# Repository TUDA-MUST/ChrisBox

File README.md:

# ChrisBox
(**CH**arge **R**eading **I**nferface **S**ystem Box)\
4-Channel Charge Amplifier PCB

## Introduction

Welcome to ChrisBox!\
ChrisBox is a four-channel charge amplifier, mainly developed for the simultaneous charge measurement of four ferroelectret sensors.
The main goals of the development were
- low noise (shielding concept),
- portability,
- usability,
- affordability.

More details about ChrisBox can be found [here](#about-chrisbox).

> [!IMPORTANT]
> This document describes the features and assembly of ChrisBox and does not provide guidance on constructing or using ferroelectret sensors.

## About this Repository

This repository contains the PCB design of ChrisBox, the CAD files for the Box, where the PCB can be combined with a battery and a display, as well as general code for the PCB.
- [PCB](/PCB) -> circuit board
- [CAD](/CAD) -> housing for the circuit board and an additional display
- [CODE](/CODE) -> code to be flashed on the microcontroller of the PCB, and code for a Nextion display.

A code description is found in the `./CODE` folder, if you just want to build a ChrisBox, the following instructions should be sufficient.

Ordering and Building instructions are included here:
- [ORDERING INSTRUCTIONS](/ORDERING_INSTRUCTIONS.md)
- [BUILDING INSTRUCTIONS](/BUILDING_INSTRUCTIONS.md)

Contributing to ChrisBox and this repository: [CONTRIBUTORS](#contributors).\
License: [LICENSE](/LICENSE).

Information about citation is found here: [CITATION](#citation).

## About ChrisBox

### Development objective and target group

Piezoelectric sensors convert electric charge in response to mechanical loading and are widely studied for their high sensitivity.
In particular, ferroelectret sensors provide the flexibility and material system design that enable biocompatibility.
These signals are typically captured using commercial electrometers or custom-built charge amplifiers to enable portability.
However, the latter often lack the precision and robustness against electromagnetic interference (EMI).
Therefore, we present a compact, four-channel portable measurement system specifically designed for charge-based force sensing with piezoelectric sensors, called ChrisBox.
The system has been developed at the **Measurement and Sensor Technology Group** at **Technische Universität Darmstadt**, Darmstadt, Germany.

The main goals of the development were:
- **Low noise:** achieved through a shielding concept that covers the PCB, the cable to the sensor, and, depending on the sensor, the sensor itself.
- **Portability:** a key advantage over traditional electrometers and oscilloscopes, enabling measurements on the human body while walking or performing other movements.
- **Usability:** the PCB is designed for users without expertise in PCB development or programming, allowing straightforward measurements with ferroelectret sensors.
- **Affordability:** one assembled PCB costs roughly 50 euros in 2025, facilitating reproduction and simultaneous use while avoiding the need for expensive laboratory instruments such as electrometers.

### Detailed decription of ChrisBox

**Analog electronics**
A ferroelectret is connected to the PCB via a USB-C cable and connector.
The signal wires, D+ and D-, carry the charge displacement generated by the ferroelectret, which is converted into a voltage signal by a charge amplifier.
An exemplary application of this setup is heart rate measurement, which requires low-frequency measurements.
Therefore, a large feedback resistor (in the G&Omega; range) is used in the charge amplifier.
A reference voltage at the midpoint of the measurement range (around 1.65 V) is provided to enable differential measurements within the 0–3.3 V range.
The analog electronics are replicated four times, with each channel operating independently.

**Digital electronics**
The output of each charge amplifier is connected to an ADC (ADS1220).
The reference voltage is also supplied to the ADC to enable differential measurements.
All four ADCs communicate with an ESP32 via SPI.

**ESP32**
An ESP32 S3 Mini 1 serves as the microcontroller of the ChrisBox, accompanied by Boot and Reset buttons.
A UART-to-USB converter ensures reliable connectivity with various PCs.

**Support circuits**
The PCB includes several additional circuits: four programmable status LEDs controlled by the ESP32, a UART connector for interfacing with a Nextion display, and a connector providing access to five GPIO pins of the ESP32 for custom functions.
A 5 V supply, switchable by the ESP32, can power the Nextion display.
A battery can be connected for power supply and is simultaneously charged when the board is connected to USB.

**Shielding**
The PCB is shielded by a metallic frame and cover, as well as an internal shielding layer within the board.
USB-C cables are used to connect the ferroelectret sensors, as they are both shielded and readily available.
Each ferroelectret sensor must be soldered to a USB-C connector.
Since an unshielded ferroelectret sensor can act as a source of noise, proper shielding is essential to ensure a low-noise measurement setup.

**Data output**
The acquired measurement data can be output in several ways:
- Serial communication to a PC,
- UART connection to a Nextion display for real-time visualization,
- ESP-NOW for wireless data transmission, requiring a second ESP32 as receiver for the data, which itself could communicate to a PC.

## Contributors

ChrisBox was developed at the [Measurement and Sensor Technology Group](https://www.etit.tu-darmstadt.de/must/) at Technische Universität Darmstadt, Germany, by:
- [Sven Suppelt](https://orcid.org/0000-0002-2338-9333)
- [Dominik Werner](https://orcid.org/0009-0001-8082-5584)
- [Alexander A. Altmann](https://orcid.org/0000-0001-5299-3620)
- [Felix Herbst](https://orcid.org/0000-0003-1480-3691)
- [Jan H. Dörsam](https://orcid.org/0000-0001-9807-6641)
- [Bastian Latsch](https://orcid.org/0000-0001-9929-5694)
- [Prof. Mario Kupnik](https://orcid.org/0000-0003-2287-4481)

## Citation

If you would like to reference the project, please cite DOI: [10.3390/hardware4040020](https://doi.org/10.3390/hardware4040020).

```
@article{hardware4040020,
  author = {Suppelt, Sven and Werner, Dominik and Altmann, Alexander Anton and Herbst, Felix and Ulmer, Lukas and Dörsam, Jan Helge and Latsch, Bastian and Kupnik, Mario},
  title = {ChrisBox: An Open-Source 4-Channel Portable Charge Amplifier for Research and Education},
  journal = {Hardware},
  year = {2026},
  volume = {4},
  number = {4},
  pages = {20},
  doi = {10.3390/hardware4040020}
}
```

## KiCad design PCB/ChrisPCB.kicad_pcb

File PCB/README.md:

# PCB

Welcome to the PCB folder of ChrisBox!
The ChrisBox PCB is designed with KiCad. The Project files and generated Exports are found here.

## Content of the PCB folder

- `./data` - pictures of the PCB and some for the schematic and silkscreen.
- `./exports` - The `.step`-export of the ChrisBox PCB.
- `./interactive bom` - The interactive HTML BOM (made with Interactive Html Bom). It is useful for handsoldering or just looking up which component has to go where.
- `./jlcpcb` - Output data from the KiCAD JLCPCB tools. This data can be used for ordering a PCB with components. Always re-check the data yourself!
- `./models` - Additional footprints and models, which are not included in KiCad and its plugins itself.

The other files in this folder are the [main KiCad project](/PCB/ChrisPCB.kicad_pro) with schematic and pcb, as well as the sub-schematics (ferro_amplifier and usb_connector).

## Notes on KiCad settings

The design was made with KiCad 8.0. Installed plugins are the Alternate KiCad Library (by Dawid Cislo), the Interactive Html Bom (by qu1ck) and the KiCAD JLCPCB tools (by Bouni).
Additional Footprints or 3D models are found in the `./models` folder.\
Always check the JLCPCB options yourself! The tools seemed to "forget" some data from time to time.

## Ordering and building the PCB

For ordering instructions refer to [ORDERING INSTRUCTIONS](/ORDERING_INSTRUCTIONS.md).
For building instructions refer to [BUILDING INSTRUCTIONS](/BUILDING_INSTRUCTIONS.md).

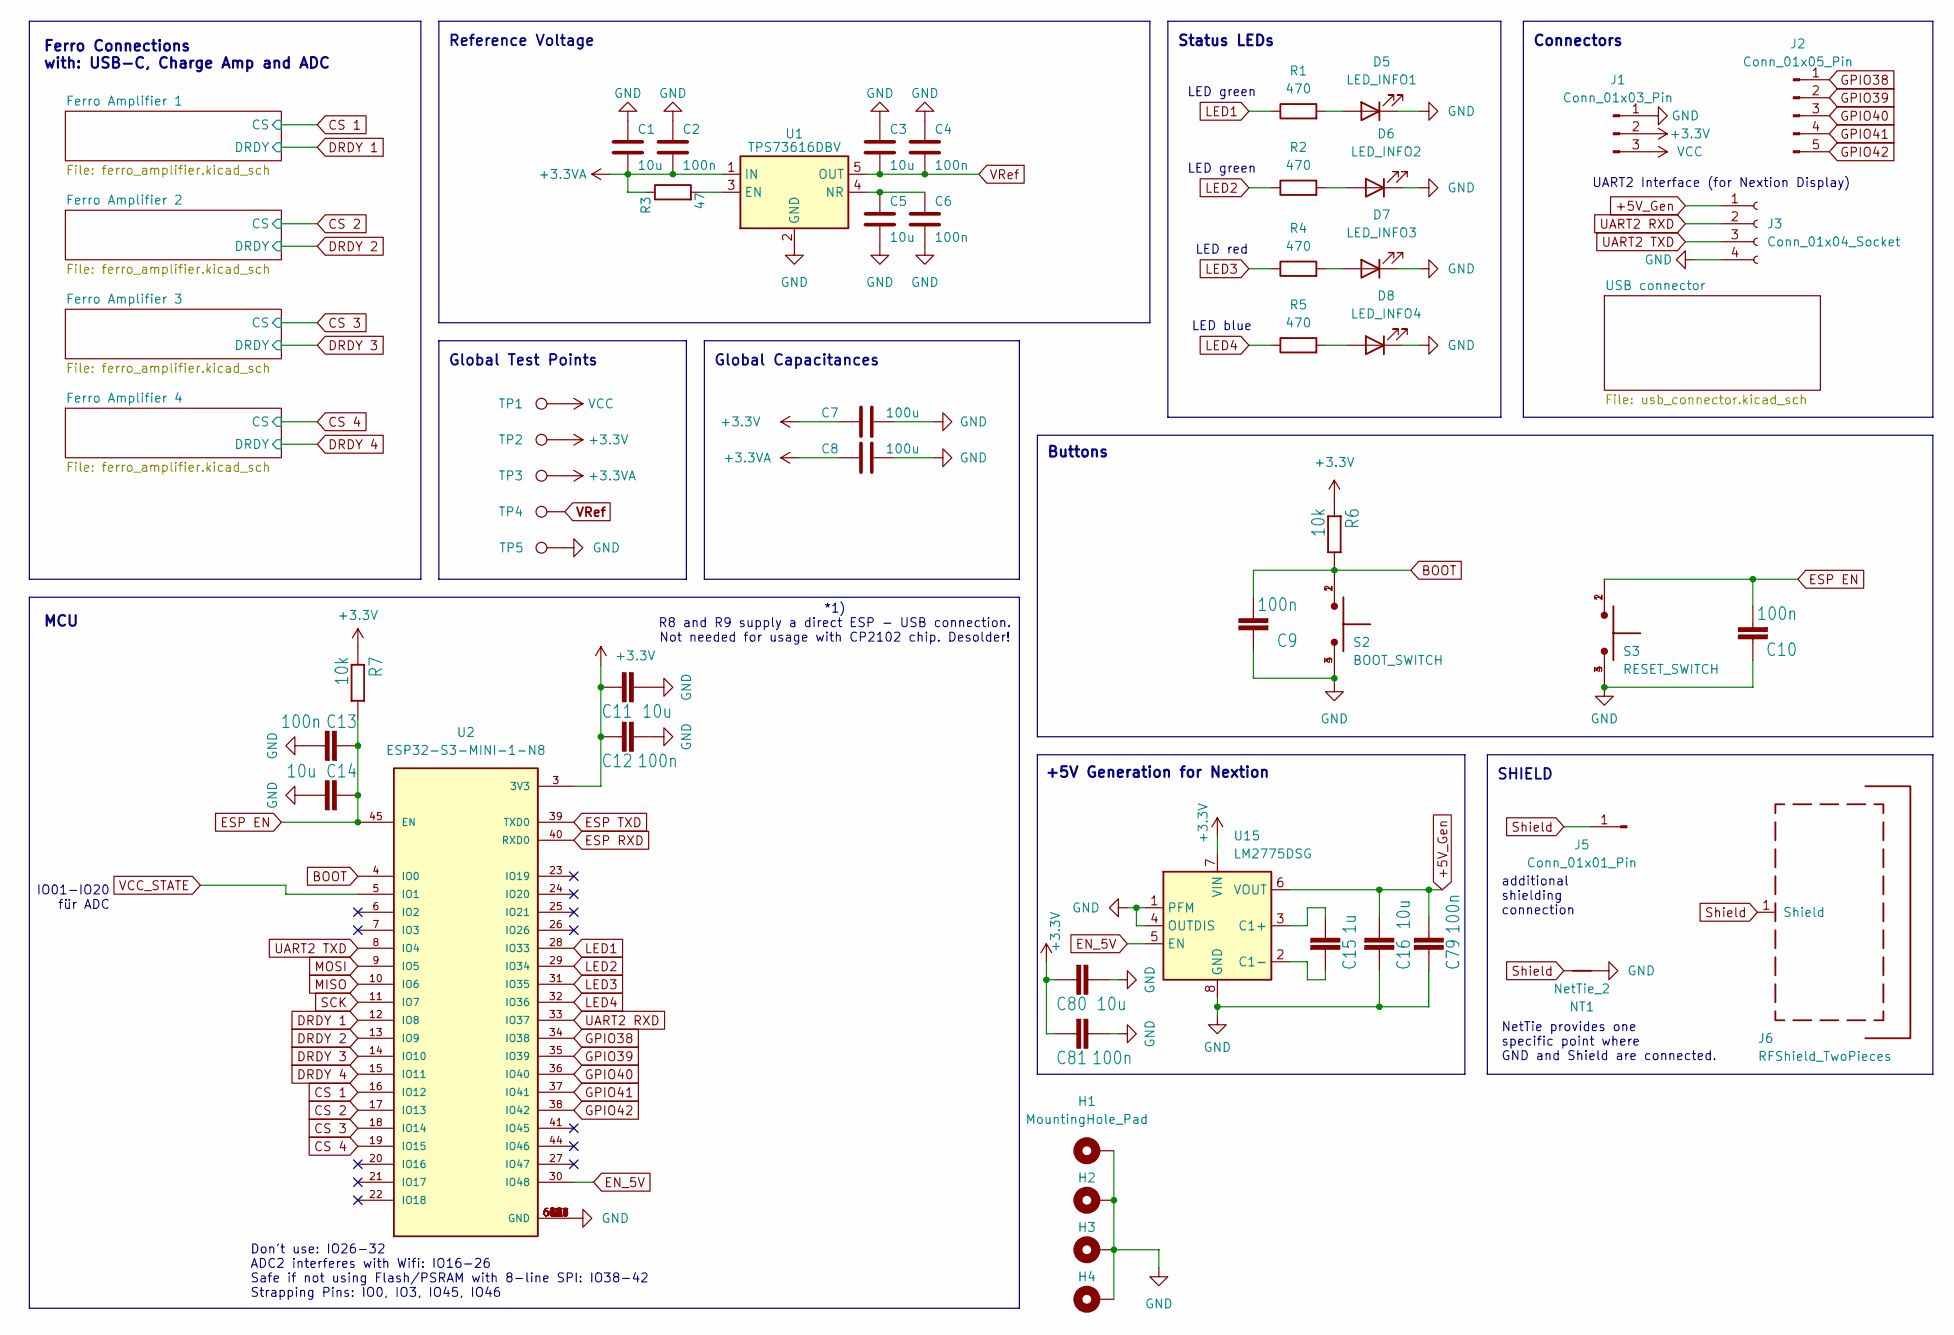
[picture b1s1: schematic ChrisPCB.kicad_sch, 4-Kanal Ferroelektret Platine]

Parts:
C1, C3, C5, C11, C14, C16, C80: 10u; C_0402_1005Metric
C2, C4, C6, C9, C10, C12, C13, C79, C81: 100n; C_0402_1005Metric
C7, C8: 100u; C_1206_3216Metric
C15: 1u; C_0402_1005Metric
D5: LED_INFO1; LED_0402_1005Metric
D6: LED_INFO2; LED_0402_1005Metric
D7: LED_INFO3; LED_0402_1005Metric
D8: LED_INFO4; LED_0402_1005Metric
H1, H2, H3, H4: MountingHole_Pad; MountingHole_3.2mm_M3_Pad
J1: Conn_01x03_Pin; PinHeader_1x03_P2.54mm_Vertical
J2: Conn_01x05_Pin; PinHeader_1x05_P2.54mm_Vertical
J3: Conn_01x04_Socket; JST_XH_B4B-XH-A_1x04_P2.50mm_Vertical
J5: Conn_01x01_Pin; PinHeader_1x01_P2.54mm_Vertical
J6: RFShield_TwoPieces; Laird_Technologies_BMI-S-205-F_38.10x25.40mm_HandSolder_Sel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
NT1: NetTie_2; NetTie-2_SMD_Pad0.5mm
R1, R2, R4, R5: 470; R_0402_1005Metric
R3: 47; R_0402_1005Metric
R6, R7: 10k; R_0402_1005Metric
S2: BOOT_SWITCH; SW_SKRPABE010
S3: RESET_SWITCH; SW_SKRPABE010
TP1, TP2, TP3, TP4, TP5: TestPoint; TestPoint_THTPad_D1.5mm_Drill0.7mm
U1: TPS73616DBV; SOT-23-5
U2: ESP32-S3-MINI-1-N8; XCVR_ESP32-S3-MINI-1-N8; PARTREV v0.6
U15: LM2775DSG; WSON-8-1EP_2x2mm_P0.5mm_EP0.9x1.6mm_ThermalVias

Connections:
+3.3V: C7.1, C11.2, C12.2, C80.2, C81.2, J1.2, R6.1, R7.1, TP2.1, U2.3 (3V3), U15.7 (VIN); also elsewhere on the board
+3.3VA: C1.2, C2.2, C8.1, R3.1, TP3.1, U1.1 (IN); also elsewhere on the board
+5V_Gen: C16.1, C79.1, J3.1, U15.6 (VOUT)
BOOT: C9.2, R6.2, S2.1, S2.2, U2.4 (IO0); also elsewhere on the board
CS 1: U2.16 (IO12); also elsewhere on the board
CS 2: U2.17 (IO13); also elsewhere on the board
CS 3: U2.18 (IO14); also elsewhere on the board
CS 4: U2.19 (IO15); also elsewhere on the board
DRDY 1: U2.12 (IO8); also elsewhere on the board
DRDY 2: U2.13 (IO9); also elsewhere on the board
DRDY 3: U2.14 (IO10); also elsewhere on the board
DRDY 4: U2.15 (IO11); also elsewhere on the board
EN_5V: U2.30 (IO48), U15.5 (EN)
ESP EN: C10.2, C13.2, C14.2, R7.2, S3.1, S3.2, U2.45 (EN); also elsewhere on the board
ESP RXD: U2.40 (RXD0); also elsewhere on the board
ESP TXD: U2.39 (TXD0); also elsewhere on the board
GND: C1.1, C2.1, C3.1, C4.1, C5.2, C6.2, C7.2, C8.2, C9.1, C10.1, C11.1, C12.1, C13.1, C14.1, C16.2, C79.2, C80.1, C81.1, D5.1 (K), D6.1 (K), D7.1 (K), D8.1 (K), H1.1, H2.1, H3.1, H4.1, J1.1, J3.4, NT1.1, S2.3, S2.4, S3.3, S3.4, TP5.1, U1.2 (GND), U2.1 (GND), U2.2 (GND), U2.42 (GND), U2.43 (GND), U2.46 (GND), U2.47 (GND), U2.48 (GND), U2.49 (GND), U2.50 (GND), U2.51 (GND), U2.52 (GND), U2.53 (GND), U2.54 (GND), U2.55 (GND), U2.56 (GND), U2.57 (GND), U2.58 (GND), U2.59 (GND), U2.60 (GND), U2.61 (GND), U2.61_1 (GND), U2.61_2 (GND), U2.61_3 (GND), U2.61_4 (GND), U2.61_5 (GND), U2.61_6 (GND), U2.61_7 (GND), U2.61_8 (GND), U2.62 (GND), U2.63 (GND), U2.64 (GND), U2.65 (GND), U15.1 (PFM), U15.4 (OUTDIS), U15.8 (GND), U15.9 (GND); also elsewhere on the board
GPIO38: J2.1, U2.34 (IO38)
GPIO39: J2.2, U2.35 (IO39)
GPIO40: J2.3, U2.36 (IO40)
GPIO41: J2.4, U2.37 (IO41)
GPIO42: J2.5, U2.38 (IO42)
LED1: R1.1, U2.28 (IO33)
LED2: R2.1, U2.29 (IO34)
LED3: R4.1, U2.31 (IO35)
LED4: R5.1, U2.32 (IO36)
MISO: U2.10 (IO6); also elsewhere on the board
MOSI: U2.9 (IO5); also elsewhere on the board
unnamed: D5.2 (A), R1.2
unnamed: D6.2 (A), R2.2
unnamed: D7.2 (A), R4.2
unnamed: D8.2 (A), R5.2
unnamed: R3.2, U1.3 (EN)
unnamed: C5.1, C6.1, U1.4 (NR)
unnamed: C15.1, U15.3 (C1+)
unnamed: C15.2, U15.2 (C1-)
SCK: U2.11 (IO7); also elsewhere on the board
Shield: J5.1, J6.1 (Shield), NT1.2; also elsewhere on the board
UART2 RXD: J3.2, U2.33 (IO37)
UART2 TXD: J3.3, U2.8 (IO4)
VCC: J1.3, TP1.1; also elsewhere on the board
VCC_STATE: U2.5 (IO1); also elsewhere on the board
VRef: C3.2, C4.2, TP4.1, U1.5 (OUT); also elsewhere on the board

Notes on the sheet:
+5V Generation for Nextion
Global Capacitances
Global Test Points
Buttons
LED green
Reference Voltage
Ferro Connections with: USB-C, Charge Amp and ADC
NetTie provides one specific point where GND and Shield are connected.
Status LEDs
IO01-IO20 für ADC
MCU
SHIELD
Don't use: IO26-32 ADC2 interferes with Wifi: IO16-26 Safe if not using Flash/PSRAM with 8-line SPI: IO38-42 Strapping Pins: IO0, IO3, IO45, IO46
additional shielding connection
LED blue
*1) R8 and R9 supply a direct ESP - USB connection. Not needed for usage with CP2102 chip. Desolder!
Connectors
LED red
UART2 Interface (for Nextion Display)

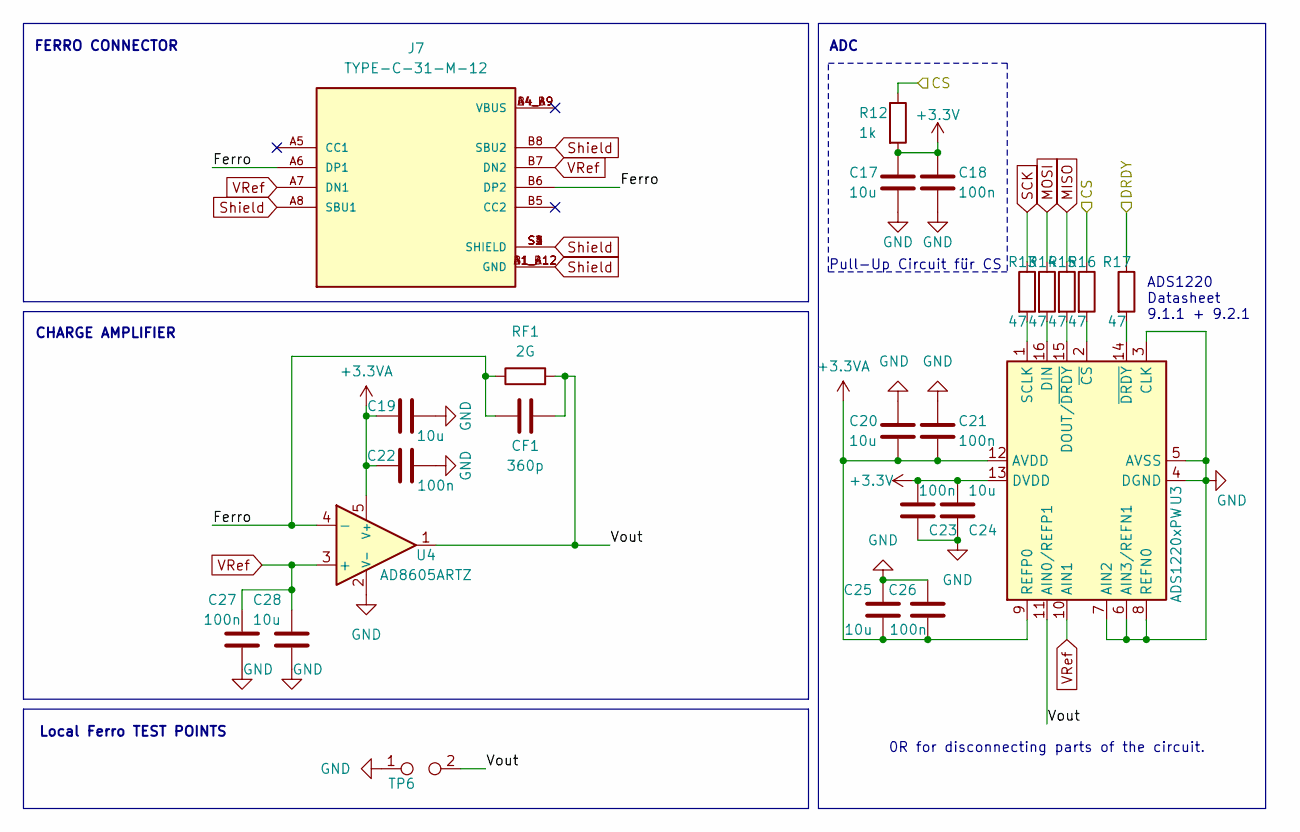
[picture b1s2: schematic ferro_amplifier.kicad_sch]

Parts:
C17, C19, C20, C24, C25, C28: 10u; C_0402_1005Metric
C18, C21, C22, C23, C26, C27: 100n; C_0402_1005Metric
CF1: 360p; C_0805_2012Metric
J7: TYPE-C-31-M-12; HRO_TYPE-C-31-M-12; PARTREV 2020.12.08
R12: 1k; R_0402_1005Metric
R13, R14, R15, R16, R17: 47; R_0402_1005Metric
RF1: 2G; R_0805_2012Metric
TP6: TestPoint_2Pole; TestPoint_2Pads_Pitch2.54mm_Drill0.8mm
U3: ADS1220xPW; TSSOP-16_4.4x5mm_P0.65mm
U4: AD8605ARTZ; SOT-23-5

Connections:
+3.3V: C17.1, C18.2, C23.2, C24.1, R12.2, U3.13 (DVDD); also elsewhere on the board
+3.3VA: C19.2, C20.2, C21.1, C22.1, C25.1, C26.2, U3.9 (REFP0), U3.12 (AVDD), U4.5 (V+); also elsewhere on the board
/Ferro Amplifier 1/Ferro: CF1.1, J7.A6 (DP1), J7.B6 (DP2), RF1.1, U4.4 (-)
/Ferro Amplifier 1/Vout: CF1.2, RF1.2, TP6.2, U3.11 (AIN0/REFP1), U4.1
CS 1: R12.1, R16.1; also elsewhere on the board
DRDY 1: R17.1; also elsewhere on the board
GND: C17.2, C18.1, C19.1, C20.1, C21.2, C22.2, C23.1, C24.2, C25.2, C26.1, C27.1, C28.2, TP6.1, U3.3 (CLK), U3.4 (DGND), U3.5 (AVSS), U3.6 (AIN3/REFN1), U3.7 (AIN2), U3.8 (REFN0), U4.2 (V-); also elsewhere on the board
MISO: R15.1; also elsewhere on the board
MOSI: R14.1; also elsewhere on the board
unnamed: R14.2, U3.16 (DIN)
unnamed: R15.2, U3.15 (DOUT/~DRDY)
unnamed: R13.2, U3.1 (SCLK)
unnamed: R16.2, U3.2 (~CS)
unnamed: R17.2, U3.14 (~DRDY)
SCK: R13.1; also elsewhere on the board
Shield: J7.A1_B12 (GND), J7.A8 (SBU1), J7.B1_A12 (GND), J7.B8 (SBU2), J7.S1 (SHIELD), J7.S2 (SHIELD), J7.S3 (SHIELD), J7.S4 (SHIELD); also elsewhere on the board
VRef: C27.2, C28.1, J7.A7 (DN1), J7.B7 (DN2), U3.10 (AIN1), U4.3 (+); also elsewhere on the board

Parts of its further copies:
C29, C31, C32, C36, C37, C40, C41, C43, C44, C48, C49, C52, C53, C55, C56, C60, C61, C64: 10u; C_0402_1005Metric
C30, C33, C34, C35, C38, C39, C42, C45, C46, C47, C50, C51, C54, C57, C58, C59, C62, C63: 100n; C_0402_1005Metric
CF2, CF3, CF4: 360p; C_0805_2012Metric
J8, J9, J10: TYPE-C-31-M-12; HRO_TYPE-C-31-M-12; PARTREV 2020.12.08
R18, R24, R30: 1k; R_0402_1005Metric
R19, R20, R21, R22, R23, R25, R26, R27, R28, R29, R31, R32, R33, R34, R35: 47; R_0402_1005Metric
RF2, RF3, RF4: 2G; R_0805_2012Metric
TP7, TP8, TP9: TestPoint_2Pole; TestPoint_2Pads_Pitch2.54mm_Drill0.8mm
U5, U7, U9: ADS1220xPW; TSSOP-16_4.4x5mm_P0.65mm
U6, U8, U10: AD8605ARTZ; SOT-23-5

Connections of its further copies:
+3.3V: C29.1, C30.2, C35.2, C36.1, C41.1, C42.2, C47.2, C48.1, C53.1, C54.2, C59.2, C60.1, R18.2, R24.2, R30.2, U5.13 (DVDD), U7.13 (DVDD), U9.13 (DVDD); also elsewhere on the board
+3.3VA: C31.2, C32.2, C33.1, C34.1, C37.1, C38.2, C43.2, C44.2, C45.1, C46.1, C49.1, C50.2, C55.2, C56.2, C57.1, C58.1, C61.1, C62.2, U5.9 (REFP0), U5.12 (AVDD), U6.5 (V+), U7.9 (REFP0), U7.12 (AVDD), U8.5 (V+), U9.9 (REFP0), U9.12 (AVDD), U10.5 (V+); also elsewhere on the board
/Ferro Amplifier 2/Ferro: CF2.1, J8.A6 (DP1), J8.B6 (DP2), RF2.1, U6.4 (-)
/Ferro Amplifier 2/Vout: CF2.2, RF2.2, TP7.2, U5.11 (AIN0/REFP1), U6.1
/Ferro Amplifier 3/Ferro: CF3.1, J9.A6 (DP1), J9.B6 (DP2), RF3.1, U8.4 (-)
/Ferro Amplifier 3/Vout: CF3.2, RF3.2, TP8.2, U7.11 (AIN0/REFP1), U8.1
/Ferro Amplifier 4/Ferro: CF4.1, J10.A6 (DP1), J10.B6 (DP2), RF4.1, U10.4 (-)
/Ferro Amplifier 4/Vout: CF4.2, RF4.2, TP9.2, U9.11 (AIN0/REFP1), U10.1
CS 2: R18.1, R22.1; also elsewhere on the board
CS 3: R24.1, R28.1; also elsewhere on the board
CS 4: R30.1, R34.1; also elsewhere on the board
DRDY 2: R23.1; also elsewhere on the board
DRDY 3: R29.1; also elsewhere on the board
DRDY 4: R35.1; also elsewhere on the board
GND: C29.2, C30.1, C31.1, C32.1, C33.2, C34.2, C35.1, C36.2, C37.2, C38.1, C39.1, C40.2, C41.2, C42.1, C43.1, C44.1, C45.2, C46.2, C47.1, C48.2, C49.2, C50.1, C51.1, C52.2, C53.2, C54.1, C55.1, C56.1, C57.2, C58.2, C59.1, C60.2, C61.2, C62.1, C63.1, C64.2, TP7.1, TP8.1, TP9.1, U5.3 (CLK), U5.4 (DGND), U5.5 (AVSS), U5.6 (AIN3/REFN1), U5.7 (AIN2), U5.8 (REFN0), U6.2 (V-), U7.3 (CLK), U7.4 (DGND), U7.5 (AVSS), U7.6 (AIN3/REFN1), U7.7 (AIN2), U7.8 (REFN0), U8.2 (V-), U9.3 (CLK), U9.4 (DGND), U9.5 (AVSS), U9.6 (AIN3/REFN1), U9.7 (AIN2), U9.8 (REFN0), U10.2 (V-); also elsewhere on the board
MISO: R21.1, R27.1, R33.1; also elsewhere on the board
MOSI: R20.1, R26.1, R32.1; also elsewhere on the board
unnamed: R20.2, U5.16 (DIN)
unnamed: R21.2, U5.15 (DOUT/~DRDY)
unnamed: R19.2, U5.1 (SCLK)
unnamed: R22.2, U5.2 (~CS)
unnamed: R23.2, U5.14 (~DRDY)
unnamed: R26.2, U7.16 (DIN)
unnamed: R27.2, U7.15 (DOUT/~DRDY)
unnamed: R25.2, U7.1 (SCLK)
unnamed: R28.2, U7.2 (~CS)
unnamed: R29.2, U7.14 (~DRDY)
unnamed: R32.2, U9.16 (DIN)
unnamed: R33.2, U9.15 (DOUT/~DRDY)
unnamed: R31.2, U9.1 (SCLK)
unnamed: R34.2, U9.2 (~CS)
unnamed: R35.2, U9.14 (~DRDY)
SCK: R19.1, R25.1, R31.1; also elsewhere on the board
Shield: J8.A1_B12 (GND), J8.A8 (SBU1), J8.B1_A12 (GND), J8.B8 (SBU2), J8.S1 (SHIELD), J8.S2 (SHIELD), J8.S3 (SHIELD), J8.S4 (SHIELD), J9.A1_B12 (GND), J9.A8 (SBU1), J9.B1_A12 (GND), J9.B8 (SBU2), J9.S1 (SHIELD), J9.S2 (SHIELD), J9.S3 (SHIELD), J9.S4 (SHIELD), J10.A1_B12 (GND), J10.A8 (SBU1), J10.B1_A12 (GND), J10.B8 (SBU2), J10.S1 (SHIELD), J10.S2 (SHIELD), J10.S3 (SHIELD), J10.S4 (SHIELD); also elsewhere on the board
VRef: C39.2, C40.1, C51.2, C52.1, C63.2, C64.1, J8.A7 (DN1), J8.B7 (DN2), J9.A7 (DN1), J9.B7 (DN2), J10.A7 (DN1), J10.B7 (DN2), U5.10 (AIN1), U6.3 (+), U7.10 (AIN1), U8.3 (+), U9.10 (AIN1), U10.3 (+); also elsewhere on the board

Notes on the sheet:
0R for disconnecting parts of the circuit.
Pull-Up Circuit für CS
CHARGE AMPLIFIER
ADS1220 Datasheet 9.1.1 + 9.2.1
ADC
Local Ferro TEST POINTS
FERRO CONNECTOR

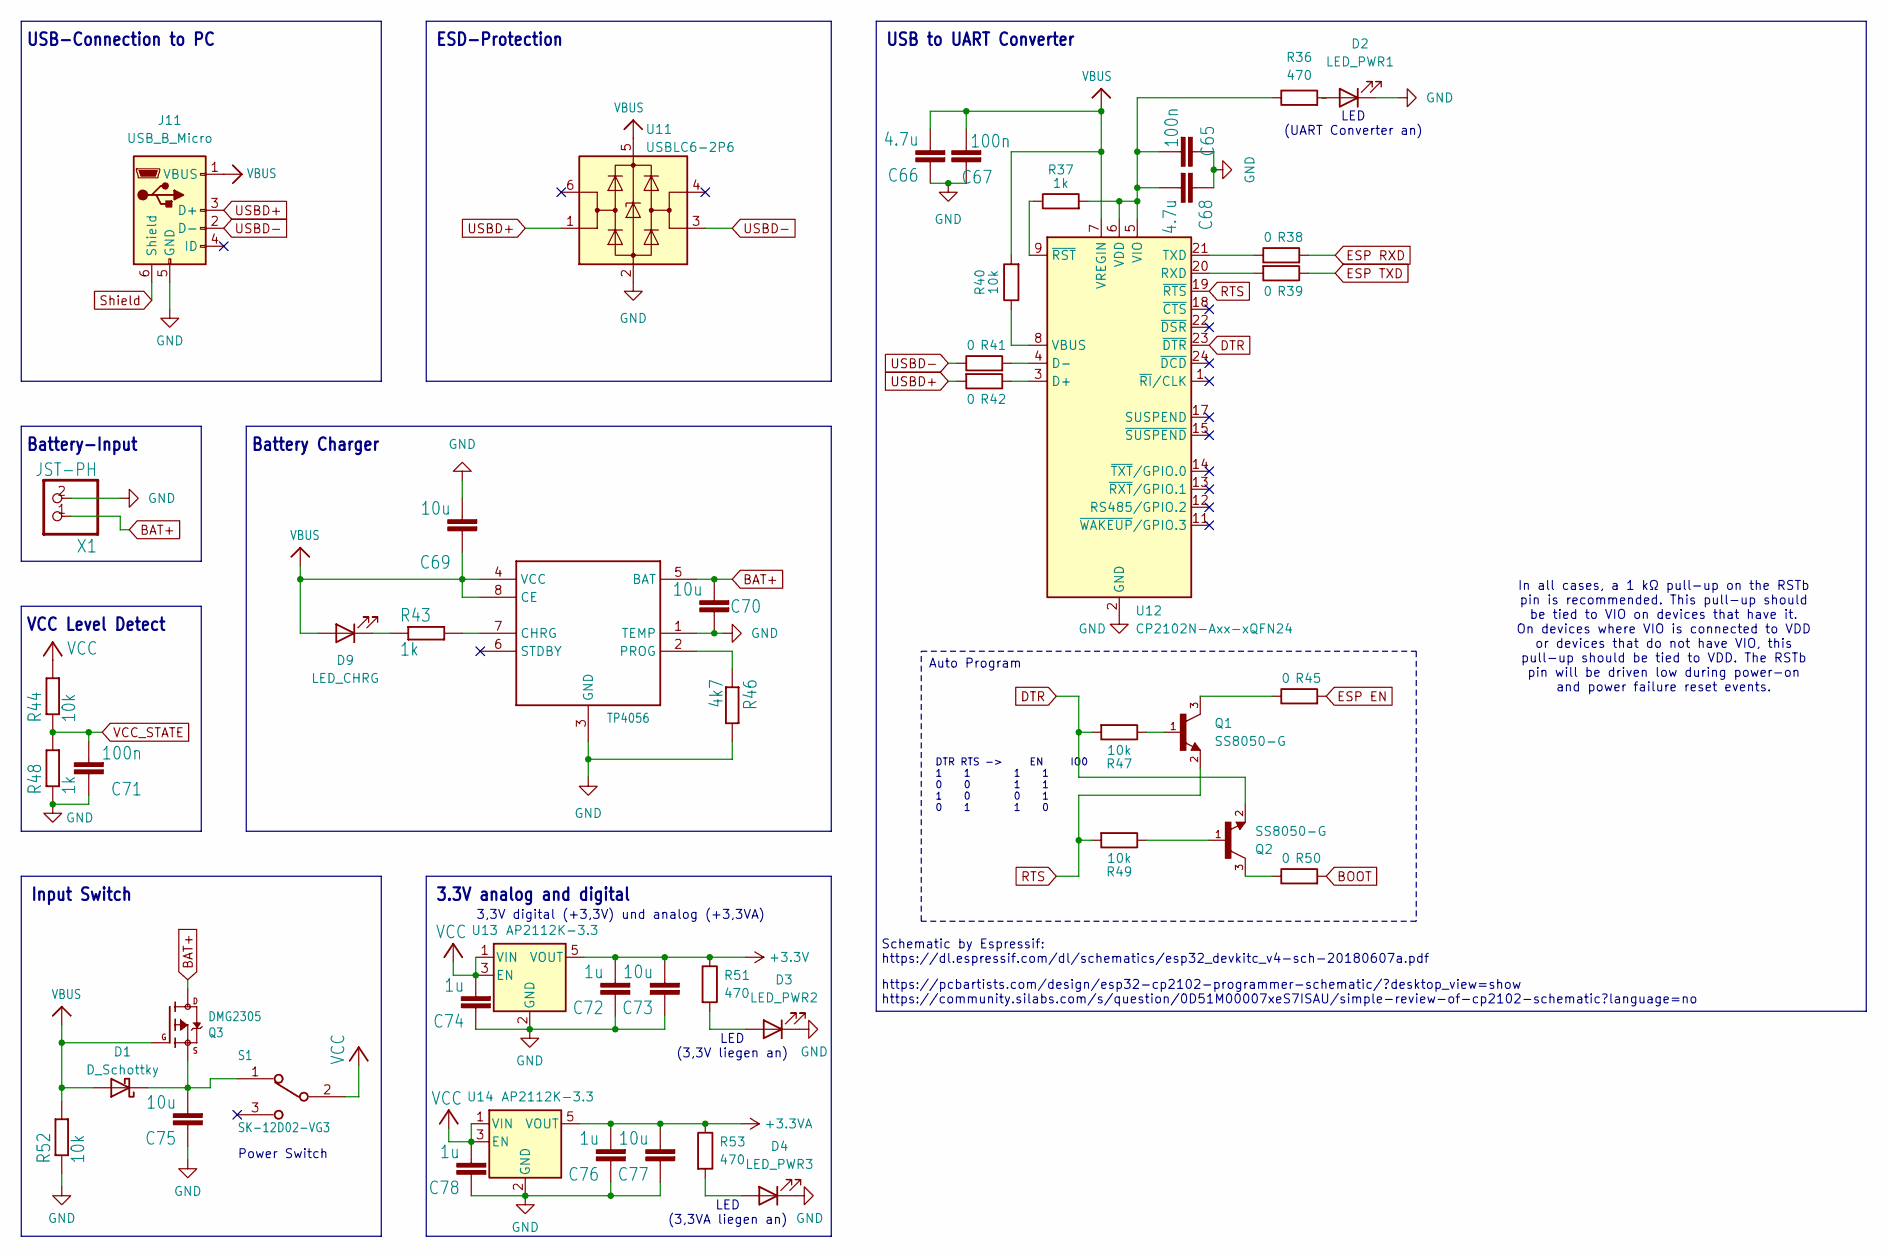
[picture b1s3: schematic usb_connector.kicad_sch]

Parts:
C65, C67, C71: 100n; C_0402_1005Metric
C66, C68: 4.7u; C_0402_1005Metric
C69, C70, C73, C75, C77: 10u; C_0402_1005Metric
C72, C74, C76, C78: 1u; C_0402_1005Metric
D1: D_Schottky; D_SMA
D2: LED_PWR1; LED_0402_1005Metric
D3: LED_PWR2; LED_0402_1005Metric
D4: LED_PWR3; LED_0402_1005Metric
D9: LED_CHRG; LED_0402_1005Metric
IC1: TP4056; SOP-8
J11: USB_B_Micro; USB_Micro-B_Molex-105017-0001
Q1, Q2: SS8050-G; TRANS_SS8050-G; PARTREV A
Q3: DMG2305; SOT-23
R36, R51, R53: 470; R_0402_1005Metric
R37, R43, R48: 1k; R_0402_1005Metric
R38, R39, R41, R42, R45, R50: 0; R_0402_1005Metric_Pad0.72x0.64mm_HandSolder
R40, R44, R47, R49, R52: 10k; R_0402_1005Metric
R46: 4k7; R_0402_1005Metric
S1: SK-12D02-VG3; SK12D02VG3
U11: USBLC6-2P6; SOT-666
U12: CP2102N-Axx-xQFN24; QFN-24-1EP_4x4mm_P0.5mm_EP2.6x2.6mm
U13, U14: AP2112K-3.3; SOT-23-5
X1: JST-PH; JST_PH_B2B-PH-K_1x02_P2.00mm_Vertical

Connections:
+3.3V: C72.2, C73.2, R51.1, U13.5 (VOUT); also elsewhere on the board
+3.3VA: C76.2, C77.2, R53.1, U14.5 (VOUT); also elsewhere on the board
BAT+: C70.2, IC1.5 (BAT), Q3.3 (D), X1.1
BOOT: R50.2; also elsewhere on the board
DTR: Q2.2, R47.2, U12.23 (~DTR)
ESP EN: R45.2; also elsewhere on the board
ESP RXD: R38.2; also elsewhere on the board
ESP TXD: R39.1; also elsewhere on the board
GND: C65.1, C66.1, C67.1, C68.1, C69.2, C70.1, C71.1, C72.1, C73.1, C74.1, C75.1, C76.1, C77.1, C78.1, D2.1 (K), D3.1 (K), D4.1 (K), IC1.1 (TEMP), IC1.3 (GND), J11.5 (GND), R46.2, R48.1, R52.1, U11.2 (GND), U12.2 (GND), U12.25 (GND), U13.2 (GND), U14.2 (GND), X1.2; also elsewhere on the board
unnamed: C75.2, D1.1 (K), Q3.2 (S), S1.1
unnamed: D2.2 (A), R36.2
unnamed: D3.2 (A), R51.2
unnamed: D4.2 (A), R53.2
unnamed: D9.1 (K), R43.1
unnamed: IC1.7 (CHRG), R43.2
unnamed: IC1.2 (PROG), R46.1
unnamed: Q1.1, R47.1
unnamed: Q1.3, R45.1
unnamed: Q2.1, R49.1
unnamed: Q2.3, R50.1
unnamed: R42.1, U12.3 (D+)
unnamed: R41.2, U12.4 (D-)
unnamed: R39.2, U12.20 (RXD)
unnamed: R38.1, U12.21 (TXD)
unnamed: R40.1, U12.8 (VBUS)
unnamed: C65.2, C68.2, R36.1, R37.2, U12.5 (VIO), U12.6 (VDD)
unnamed: R37.1, U12.9 (~RST)
RTS: Q1.2, R49.2, U12.19 (~RTS)
Shield: J11.6 (Shield); also elsewhere on the board
USBD+: J11.3 (D+), R42.2, U11.1 (I/O1)
USBD-: J11.2 (D-), R41.1, U11.3 (I/O2)
VBUS: C66.2, C67.2, C69.1, D1.2 (A), D9.2 (A), IC1.4 (VCC), IC1.8 (CE), J11.1 (VBUS), Q3.1 (G), R40.2, R52.2, U11.5 (VBUS), U12.7 (VREGIN)
VCC: C74.2, C78.2, R44.2, S1.2, U13.1 (VIN), U13.3 (EN), U14.1 (VIN), U14.3 (EN); also elsewhere on the board
VCC_STATE: C71.2, R44.1, R48.2; also elsewhere on the board

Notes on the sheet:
LED (UART Converter an)
Battery Charger
USB-Connection to PC
Auto Program
VCC Level Detect
LED (3,3V liegen an)
3,3V digital (+3,3V) und analog (+3,3VA)
Power Switch
In all cases, a 1 kΩ pull-up on the RSTb pin is recommended. This pull-up should be tied to VIO on devices that have it. On devices where VIO is connected to VDD or devices that do not have VIO, this pull-up should be tied to VDD. The RSTb pin will be driven low during power-on and power failure re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
USB to UART Converter
3.3V analog and digital
DTR RTS -> EN IO0 1 1 1 1 0 0 1 1 1 0 0 1 0 1 1 0
Battery-Input
ESD-Protection
LED (3,3VA liegen an)
Input Switch
Schematic by Espressif: https://dl.espressif.com/dl/schematics/esp32_devkitc_v4-sch-20180607a.pdf
https://pcbartists.com/design/esp32-cp2102-programmer-schematic/?desktop_view=show https://community.silabs.com/s/question/0D51M00007xeS7ISAU/simple-review-of-cp2102-schematic?language=no

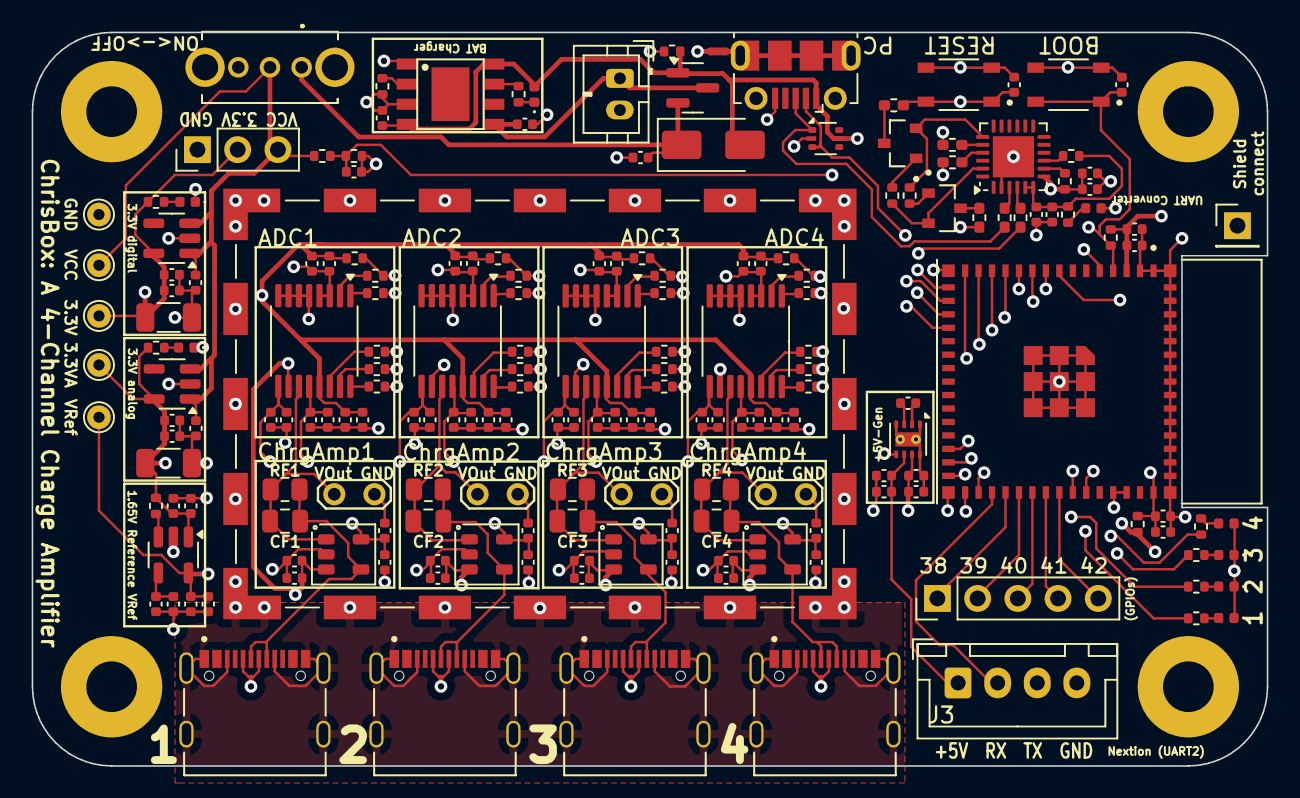
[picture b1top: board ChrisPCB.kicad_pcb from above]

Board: 4 copper layers, 78.0 x 46.3 mm, 194 parts (0 on the bottom side), 95 nets.

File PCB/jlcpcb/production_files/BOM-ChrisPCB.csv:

Comment,Designator,Footprint,LCSC,Quantity
0,"R38,R39,R41,R42,R45,R50",R_0402_1005Metric_Pad0.72x0.64mm_HandSolder,C17168,6
100n,"C10,C12,C13,C18,C2,C21,C22,C23,C26,C27,C30,C33,C34,C35,C38,C39,C4,C42,C45,C46,C47,C50,C51,C54,C57,C58,C59,C6,C62,C63,C65,C67,C71,C79,C81,C9",C_0402_1005Metric,C1525,36
100u,"C7,C8",C_1206_3216Metric,C15008,2
10k,"R40,R44,R47,R49,R52,R6,R7",R_0402_1005Metric,C25531,7
10u,"C1,C11,C14,C16,C17,C19,C20,C24,C25,C28,C29,C3,C31,C32,C36,C37,C40,C41,C43,C44,C48,C49,C5,C52,C53,C55,C56,C60,C61,C64,C69,C70,C73,C75,C77,C80",C_0402_1005Metric,C15525,36
1k,"R12,R18,R24,R30,R37,R43,R48",R_0402_1005Metric,C11702,7
1u,"C15,C72,C74,C76,C78",C_0402_1005Metric,C14445,5
2G,"RF1,RF2,RF3,RF4",R_0805_2012Metric,C2484710,4
360p,"CF1,CF2,CF3,CF4",C_0805_2012Metric,C5375895,4
4.7u,"C66,C68",C_0402_1005Metric,C23733,2
47,"R13,R14,R15,R16,R17,R19,R20,R21,R22,R23,R25,R26,R27,R28,R29,R3,R31,R32,R33,R34,R35",R_0402_1005Metric,C25118,21
470,"R1,R2,R36,R4,R5,R51,R53",R_0402_1005Metric,C25117,7
4k7,R46,R_0402_1005Metric,C25900,1
AD8605ARTZ,"U10,U4,U6,U8",SOT-23-5,C9641,4
ADS1220xPW,"U3,U5,U7,U9",TSSOP-16_4.4x5mm_P0.65mm,C48263,4
AP2112K-3.3,"U13,U14",SOT-23-5,C51118,2
BOOT_SWITCH,S2,SW_SKRPABE010,C778166,1
CP2102N-Axx-xQFN24,U12,QFN-24-1EP_4x4mm_P0.5mm_EP2.6x2.6mm,C969151,1
Conn_01x04_Socket,J3,JST_XH_B4B-XH-A_1x04_P2.50mm_Vertical,C144395,1
DMG2305,Q3,SOT-23,C2940629,1
D_Schottky,D1,D_SMA,C163541,1
ESP32-S3-MINI-1-N8,U2,XCVR_ESP32-S3-MINI-1-N8,C3013941,1
JST-PH,X1,JST_PH_B2B-PH-K_1x02_P2.00mm_Vertical,C131337,1
LED_CHRG,D9,LED_0402_1005Metric,C2852592,1
LED_INFO1,D5,LED_0402_1005Metric,C434449,1
LED_INFO2,D6,LED_0402_1005Metric,C434449,1
LED_INFO3,D7,LED_0402_1005Metric,C2844007,1
LED_INFO4,D8,LED_0402_1005Metric,C2844007,1
LED_PWR1,D2,LED_0402_1005Metric,C2852592,1
LED_PWR2,D3,LED_0402_1005Metric,C2852592,1
LED_PWR3,D4,LED_0402_1005Metric,C2852592,1
LM2775DSG,U15,WSON-8-1EP_2x2mm_P0.5mm_EP0.9x1.6mm_ThermalVias,C473361,1
RESET_SWITCH,S3,SW_SKRPABE010,C778166,1
RFShield_TwoPieces,J6,Laird_Technologies_BMI-S-205-F_38.10x25.40mm_HandSolder_SelfMade,C7429170,1
SK-12D02-VG3,S1,SK12D02VG3,C136723,1
SS8050-G,"Q1,Q2",TRANS_SS8050-G,C164886,2
TP4056,IC1,SOP-8,C16581,1
TPS73616DBV,U1,SOT-23-5,C115797,1
TYPE-C-31-M-12,"J10,J7,J8,J9",HRO_TYPE-C-31-M-12,C165948,4
USBLC6-2P6,U11,SOT-666,C2827693,1
USB_B_Micro,J11,USB_Micro-B_Molex-105017-0001,C505111,1
Conn_01x05_Pin,J2,PinHeader_1x05_P2.54mm_Vertical,,1
TestPoint,TP1,TestPoint_THTPad_D1.5mm_Drill0.7mm,,1
TestPoint,TP5,TestPoint_THTPad_D1.5mm_Drill0.7mm,,1
TestPoint,TP3,TestPoint_THTPad_D1.5mm_Drill0.7mm,,1
Conn_01x01_Pin,J5,PinHeader_1x01_P2.54mm_Vertical,,1
Conn_01x03_Pin,J1,PinHeader_1x03_P2.54mm_Vertical,,1
TestPoint,TP4,TestPoint_THTPad_D1.5mm_Drill0.7mm,,1
TestPoint,TP2,TestPoint_THTPad_D1.5mm_Drill0.7mm,,1

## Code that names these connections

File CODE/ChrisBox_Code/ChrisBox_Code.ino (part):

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#define SS      12  // Chip Select for ADC1, usable for SPI.begin(); -> for library. Later only the CS_Pins-array is used for CS pins.

// LEDs
#define LED1 33   // LED Green    -> status indicator if program is working
#define LED2 34   // LED Green    -> battery status indicator, blinking if VCC is below a threshold
#define LED3 35   // LED Blue     -> status indicator if UART2 is connected/working
#define LED4 36   // LED Blue     -> status indicator if ESP NOW is connected

#define VCC 1       // VCC, measured with internal ADC of ESP32

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#define UART2RXD 37

// 5V generation enable
#define EN_5V 48

//-------------------------------------------------------------------------------------------------------------------
// Settings and constants
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
  // -------------------------------------------------------
  // 5V generation setup
  pinMode(EN_5V, OUTPUT);         // 5V generation pin is output
  if (voltage_generation) {
    digitalWrite(EN_5V, HIGH);    // 5V shall be generated
    delay(200);                   // Delay that the display or other connected device can start.
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
  // -------------------------------------------------------

  pinMode(LED1, OUTPUT);        // LEDs as digital output pins (Program working)
  pinMode(LED2, OUTPUT);        // ...  (Battery Status)
  pinMode(LED3, OUTPUT);        // ...  (UART2 connected)
  pinMode(LED4, OUTPUT);        // ...  (ESP NOW connected)

  startupLEDshow();             // Little lightshow at the start, because it is cool.
  
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
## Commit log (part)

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2025-05-20 Folder Structure
2025-05-28 Initial push and WIP PCB
2025-05-28 PCB Routing done
2025-05-30 Fixed .gitignore, 3D-Models are now included
2025-06-02 JLCPCB Tool ausgefüllt
2025-06-05 Added JST-XH to BOM and Assembly List
2025-06-11 Rename ORDERING INSTRUCTIONS.md to ORDERING_INSTRUCTIONS.md
2025-06-11 Rename Readme.md to README.md
2025-06-11 PCB Ordner sortiert
2025-06-11 CAD STLs cleanup
2025-06-11 CAD cleanup
2025-06-11 Moved screws
2025-06-11 CAD rename
2025-06-11 PCB folder rename
2025-06-11 data folder rename
2025-06-17 Added Pictures and Nextion Code
2025-06-17 Added README
2025-06-17 Renamed images
2025-06-17 Weißabgleich
2025-07-02 Removed Lock-Files and also added *.lck to the gitignore
2025-07-03 Added images for JLCPCB Ordering
2025-07-28 Added ChrisBox_Code
2025-07-30 Updated VRef readout functinality
2025-08-12 Nobody cares about VCC and VREF when connected via USB.
2025-09-16 Added CAD files for case for use without nextion screen
2025-09-16 Added inscription to title image
2025-10-15 Delete PCB/data directory
    Due to copyright issues
2025-10-15 Fixed Font
2025-10-15 Added font licence file
2025-10-15 Update LICENSE
2025-10-15 Create NOTICE
2025-11-05 Remove tracking info from URLs.
2025-11-06 Correct typos.
2025-11-06 Polish readme,
    insert parts from paper abstract, harmonize white space and line breaks.
